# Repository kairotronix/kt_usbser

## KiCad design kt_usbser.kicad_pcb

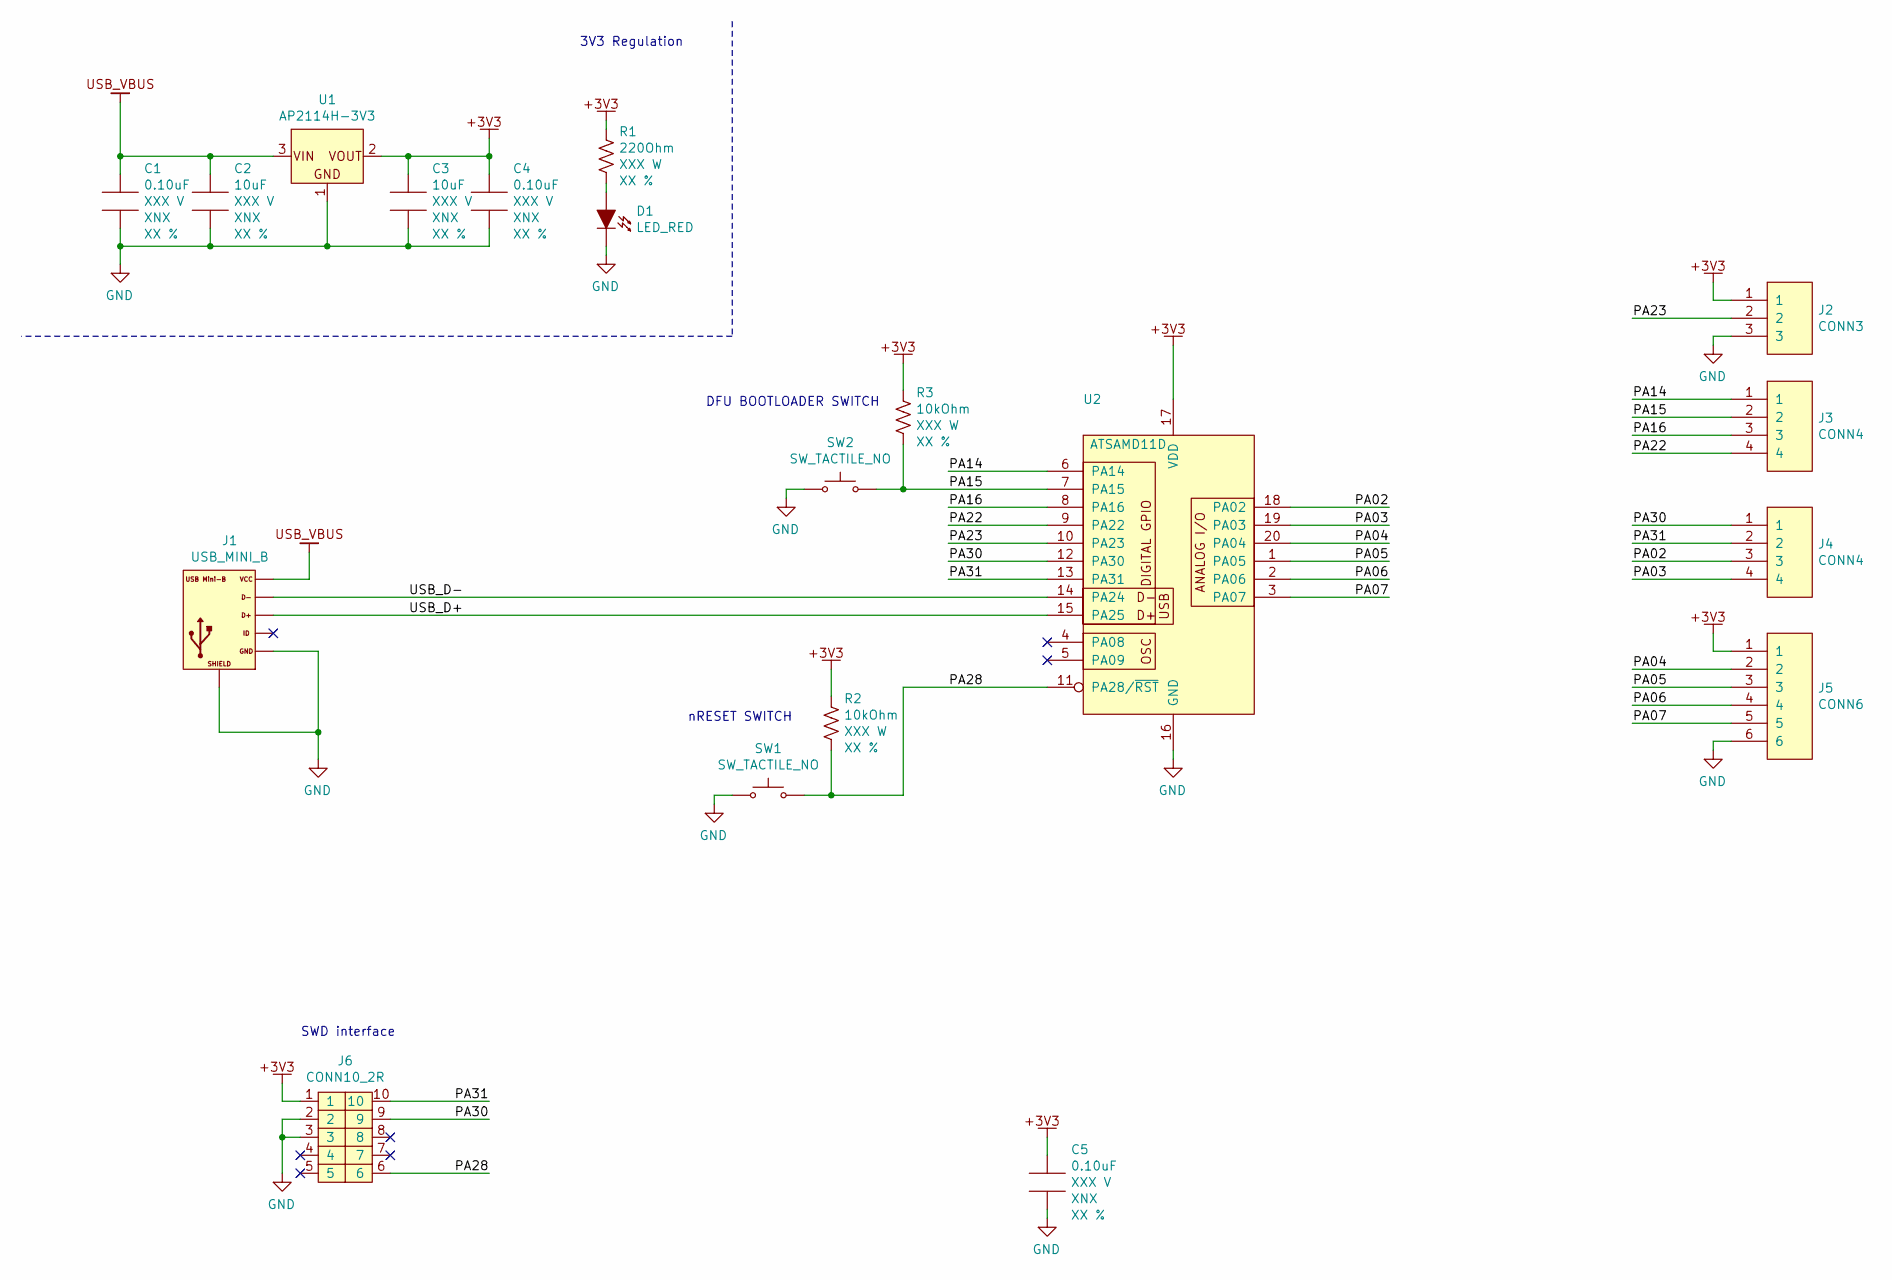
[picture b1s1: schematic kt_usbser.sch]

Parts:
C1, C4, C5: 0.10uF; CAP_0603; Voltage XXX V; Tolerance XX %
C2, C3: 10uF; CAP_0603; Voltage XXX V; Tolerance XX %
D1: LED_RED; LED_0805
J1: USB_MINI_B; USB_MINIB_THT_TE_2172034-1
J2: CONN3; 1x03_0.1inch_vertical_header
J3, J4: CONN4; 1x04_0.1inch_vertical_header
J5: CONN6; 1x06_0.1inch_vertical_header
J6: CONN10_2R; VERT_2R_10POS_1P27MM
R1: 220Ohm; RES_0603; Tolerance XX %
R2, R3: 10kOhm; RES_0603; Tolerance XX %
SW1, SW2: SW_TACTILE_NO; 5p2x5p2_SMD; MFG1 P/N PTS526 SMG15 SMTR2 LFS
U1: AP2114H-3V3; SOT-223; MFG P/N AP2114H-3.3TRG1
U2: ATSAMD11D; SOIC-20; MFG1 P/N ATSAMD11D14A-SSUT

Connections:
3V3: C3.1, C4.1, C5.1, J2.1, J5.1, J6.1, R1.1, R2.1, R3.1, U1.2 (VOUT), U1.4 (VOUT), U2.17 (VDD)
/PA02: J4.3, U2.18 (PA02)
/PA03: J4.4, U2.19 (PA03)
/PA04: J5.2, U2.20 (PA04)
/PA05: J5.3, U2.1 (PA05)
/PA06: J5.4, U2.2 (PA06)
/PA07: J5.5, U2.3 (PA07)
/PA14: J3.1, U2.6 (PA14)
/PA15: J3.2, R3.2, SW2.3, SW2.4, U2.7 (PA15)
/PA16: J3.3, U2.8 (PA16)
/PA22: J3.4, U2.9 (PA22)
/PA23: J2.2, U2.10 (PA23)
/PA28: J6.6, R2.2, SW1.3, SW1.4, U2.11 (PA28/~RST)
/PA30: J4.1, J6.9, U2.12 (PA30)
/PA31: J4.2, J6.10, U2.13 (PA31)
/USB_D+: J1.3, U2.15 (PA25)
/USB_D-: J1.2, U2.14 (PA24)
GND: C1.2, C2.2, C3.2, C4.2, C5.2, D1.2, J1.5, J1.SHIELD, J2.3, J5.6, J6.2, J6.3, SW1.1, SW1.2, SW2.1, SW2.2, U1.1 (GND), U2.16 (GND)
unnamed: D1.1, R1.2
USB_VBUS: C1.1, C2.1, J1.1, U1.3 (VIN)

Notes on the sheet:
3V3 Regulation
nRESET SWITCH
DFU BOOTLOADER SWITCH
SWD interface

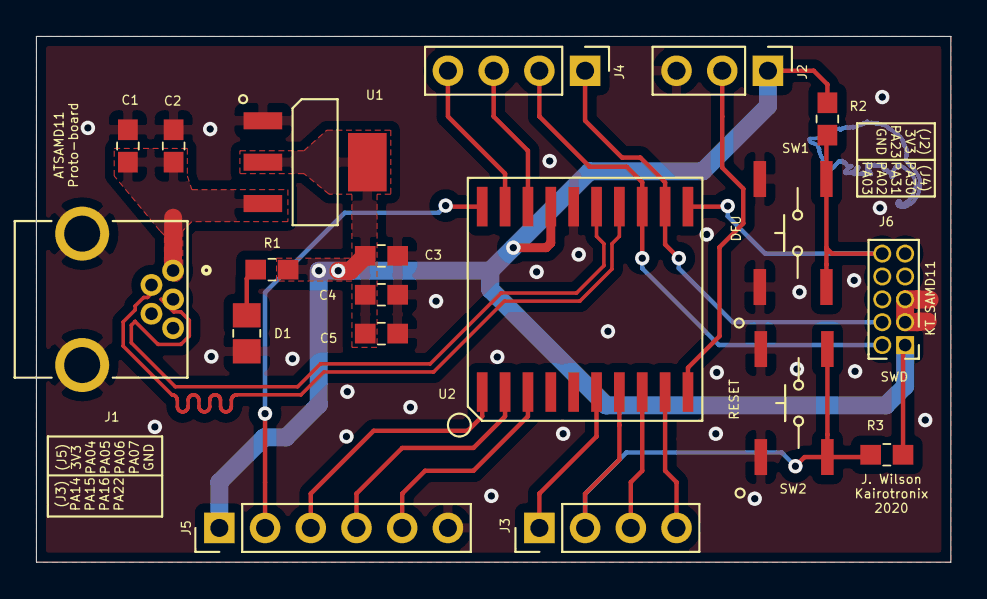
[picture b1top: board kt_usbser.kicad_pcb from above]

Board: 2 copper layers, 50.8 x 29.2 mm, 19 parts (0 on the bottom side), 20 nets.

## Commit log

2020-10-05 Initial upload of finished PCB. Should do some cleanup probably.
